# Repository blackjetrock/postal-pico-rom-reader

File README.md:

# Postal Pico ROM Reader

This is a ROM reader that is designed to be an easy to use, simple ROM dumping tool.
It should be possible to send the dumper to someone in the post, have them plug a ROM in and get
a dump of that ROM stored in the device flash. The device can then optionally dump
more ROMs and then be sent back to the person who wants the dumps. The dumps are then extracted from the 
device flash.

 <b>*** NOTE: Make sure pin 1 of the ROM is correctly aligned with pin 1 on the socket when inserting it ***</b>

The dumper can also dump ROM contents to the USB port it is powered by.

Hardware
========

The dumper is basically just a Pico attached to a ROM socket with serial resistors. It is making use of the 
possible/probably 5V tolerance of its GPIO lines-*-. The control signals are attached through low value 
resistors as they drive the ROM and aren't subject to 5V. The data lines are 5V and come into the Pico
though cowardly 28K resistors. 

Firmware
========

The firmware uses the USB serial port for interactions with the user. It uses the flash of the Pico for firmware 
and also has configuration data stored in part of the flash. ROM dumps stored in several 'slots' of 16K each so
an external non-volatile device isn't needed.
the USB serial has a menu system that can be entered at boot-up and used to set the non-volatile
configuration data that determines how the dumper will work. Slots can be cleared etc and data dumped from the menu
system.

The dumper can be set up to dump to USB or dump data to a flash slot using the configuration menu. When dumping to a 
slot the data is also dumped to USB. Once all slots are full the dumper will not over-write any slots with new dumps,
but the device can still be used as a dumper with a USB data dump.

To delete the slots a menu option is used, and several hoops have to be jumped through.

There are a couple of counters that count the number of USB dumps that the dumper has taken and the number of slot dumps it has performed.

-*-I saw a post on the internet, which if it really is by Eben Upton, says that the Pico GPIOs are
5V tolerant, but not 5V5 tolerant as inputs.

See here:

https://hackaday.com/2022/09/25/pi-pico-w-does-pcmcia-gets-this-ibm-pc110-online/#comment-6516402

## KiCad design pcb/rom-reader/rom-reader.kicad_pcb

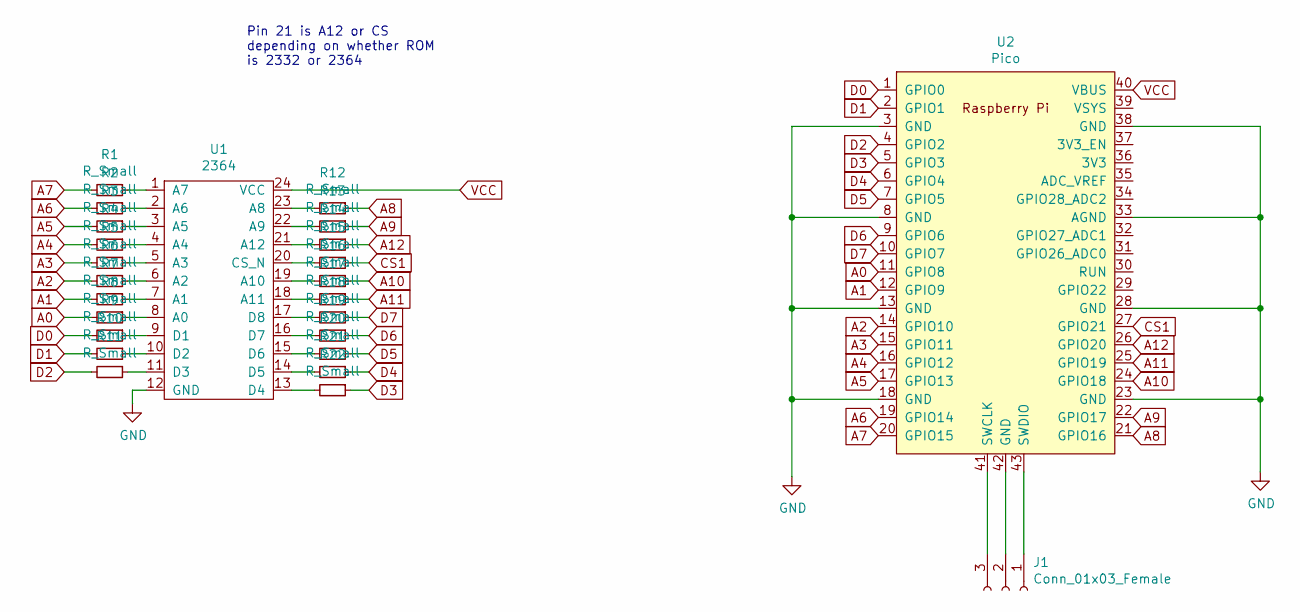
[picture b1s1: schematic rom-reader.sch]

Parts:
J1: Conn_01x03_Female; PinHeader_1x03_P2.54mm_Vertical
R1, R2, R3, R4, R5, R6, R7, R8, R9, R10, R11, R12, R13, R14, R15, R16, R17, R18, R19, R20, R21, R22: R_Small; R_0805_2012Metric_Pad1.20x1.40mm_HandSolder
U1: 2364; DIP-24_W15.24mm
U2: Pico; RPi_Pico_SMD_TH

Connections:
A0: R8.2, U2.11 (GPIO8)
A1: R7.2, U2.12 (GPIO9)
A2: R6.2, U2.14 (GPIO10)
A3: R5.2, U2.15 (GPIO11)
A4: R4.2, U2.16 (GPIO12)
A5: R3.2, U2.17 (GPIO13)
A6: R2.2, U2.19 (GPIO14)
A7: R1.2, U2.20 (GPIO15)
A8: R12.1, U2.21 (GPIO16)
A9: R13.1, U2.22 (GPIO17)
A10: R16.1, U2.24 (GPIO18)
A11: R17.1, U2.25 (GPIO19)
A12: R14.1, U2.26 (GPIO20)
CS1: R15.1, U2.27 (GPIO21)
D0: R9.2, U2.1 (GPIO0)
D1: R10.2, U2.2 (GPIO1)
D2: R11.2, U2.4 (GPIO2)
D3: R22.1, U2.5 (GPIO3)
D4: R21.1, U2.6 (GPIO4)
D5: R20.1, U2.7 (GPIO5)
D6: R19.1, U2.9 (GPIO6)
D7: R18.1, U2.10 (GPIO7)
GND: U1.12 (GND), U2.3 (GND), U2.8 (GND), U2.13 (GND), U2.18 (GND), U2.23 (GND), U2.28 (GND), U2.33 (AGND), U2.38 (GND)
unnamed: J1.1, U2.43 (SWDIO)
unnamed: J1.2, U2.42 (GND)
unnamed: J1.3, U2.41 (SWCLK)
unnamed: R1.1, U1.1 (A7)
unnamed: R2.1, U1.2 (A6)
unnamed: R3.1, U1.3 (A5)
unnamed: R4.1, U1.4 (A4)
unnamed: R5.1, U1.5 (A3)
unnamed: R6.1, U1.6 (A2)
unnamed: R7.1, U1.7 (A1)
unnamed: R8.1, U1.8 (A0)
unnamed: R9.1, U1.9 (D1)
unnamed: R10.1, U1.10 (D2)
unnamed: R11.1, U1.11 (D3)
unnamed: R12.2, U1.23 (A8)
unnamed: R13.2, U1.22 (A9)
unnamed: R14.2, U1.21 (A12)
unnamed: R15.2, U1.20 (CS_N)
unnamed: R16.2, U1.19 (A10)
unnamed: R17.2, U1.18 (A11)
unnamed: R18.2, U1.17 (D8)
unnamed: R19.2, U1.16 (D7)
unnamed: R20.2, U1.15 (D6)
unnamed: R21.2, U1.14 (D5)
unnamed: R22.2, U1.13 (D4)
VCC: U1.24 (VCC), U2.40 (VBUS)

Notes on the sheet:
Pin 21 is A12 or CS depending on whether ROM is 2332 or 2364

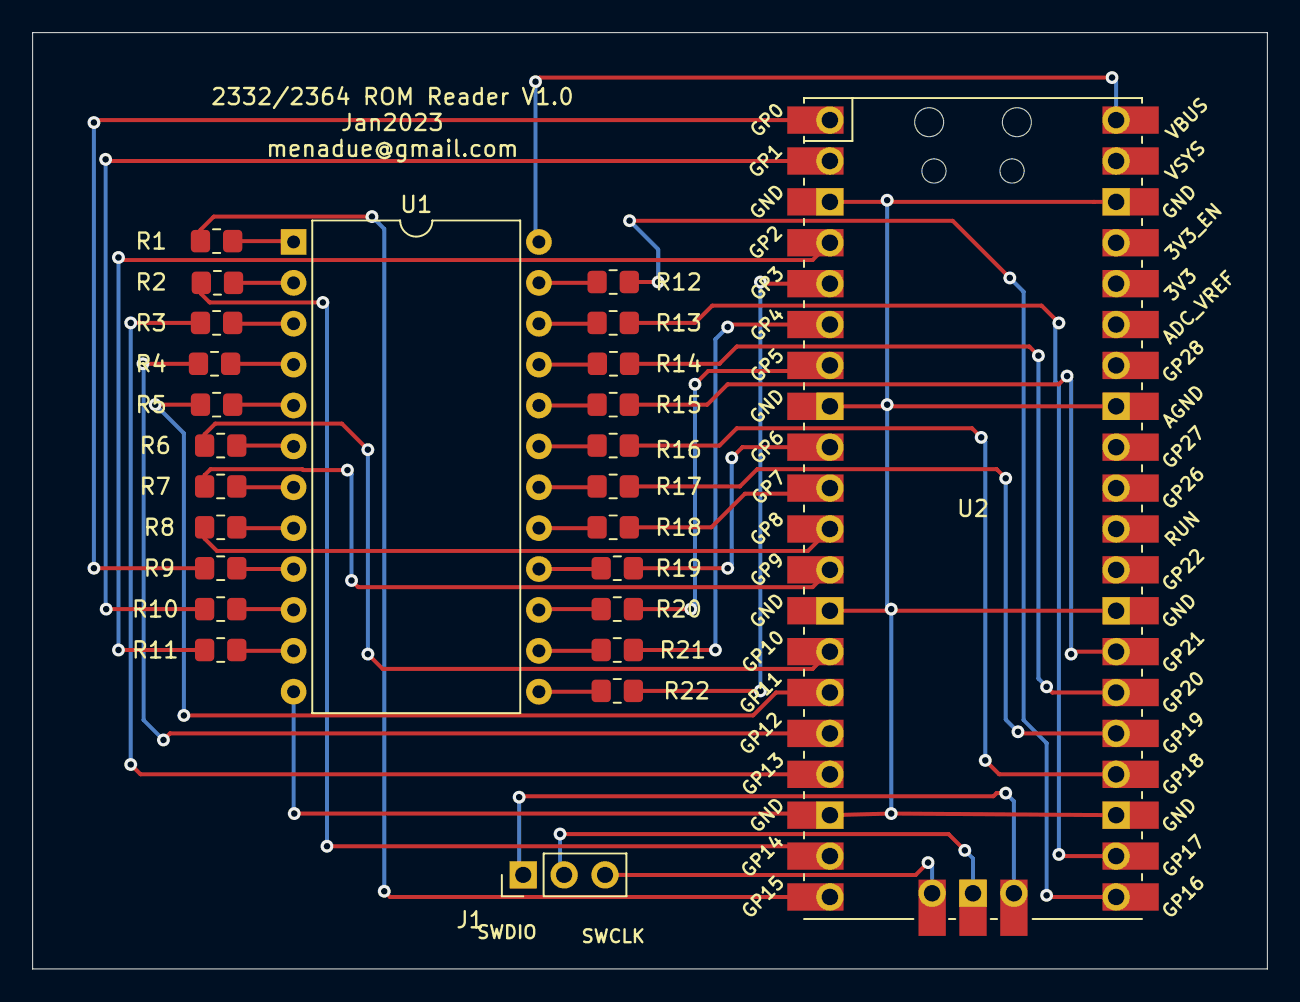
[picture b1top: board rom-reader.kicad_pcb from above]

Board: 2 copper layers, 76.7 x 58.2 mm, 25 parts (0 on the bottom side), 49 nets.

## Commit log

2023-02-03 Create LICENSE
